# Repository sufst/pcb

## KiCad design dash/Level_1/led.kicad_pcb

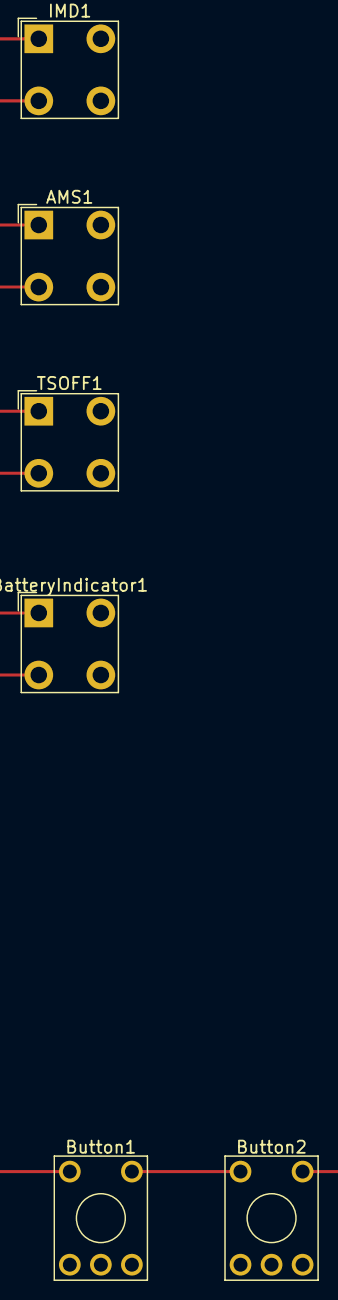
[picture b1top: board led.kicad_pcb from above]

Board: 2 copper layers, 6 parts (0 on the bottom side), 2 nets.

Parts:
AMS1: LED; LED_BL-FL7680RGB
BatteryIndicator1: LED; LED_BL-FL7680RGB
Button1: TS ON; KSA_Tactile_SPST
Button2: R2D; KSA_Tactile_SPST
IMD1: LED; LED_BL-FL7680RGB
TSOFF1: LED; LED_BL-FL7680RGB

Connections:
GND: AMS1.1, BatteryIndicator1.1, IMD1.1, TSOFF1.1
Precharge: Button1.2, Button2.1

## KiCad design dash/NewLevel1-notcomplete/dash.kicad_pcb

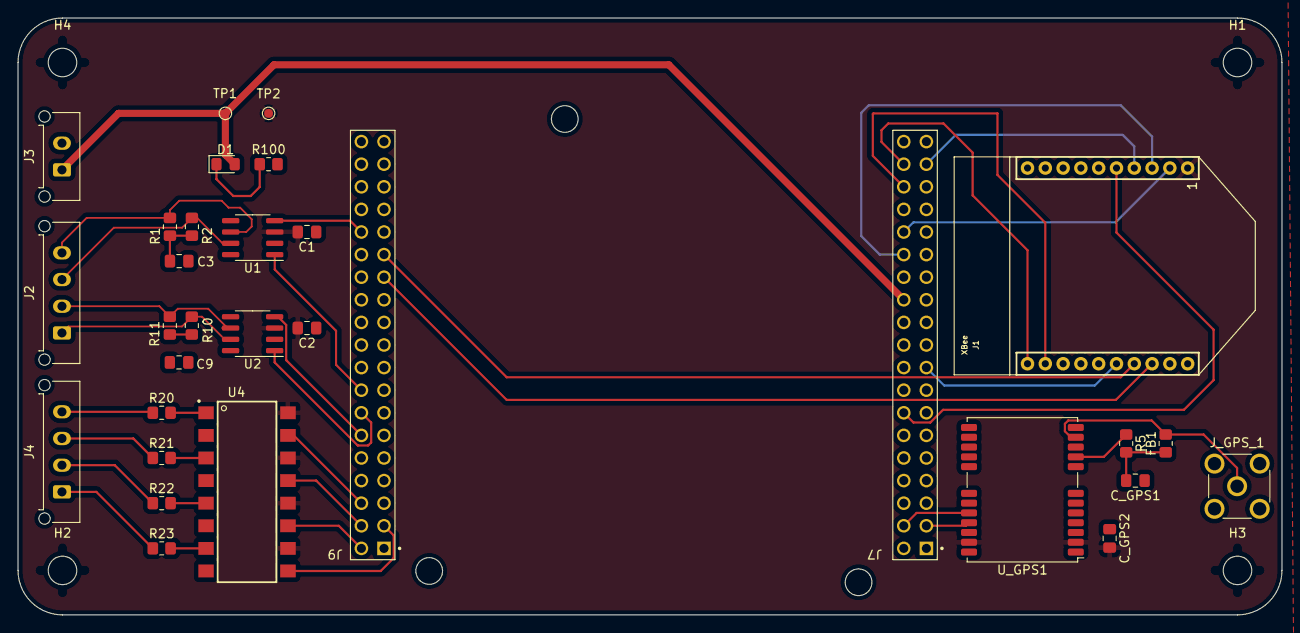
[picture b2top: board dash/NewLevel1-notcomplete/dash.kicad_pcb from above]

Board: 2 copper layers, 142.1 x 67.1 mm, 35 parts (0 on the bottom side), 40 nets.

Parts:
C1, C2: 100n; C_0805_2012Metric_Pad1.18x1.45mm_HandSolder
C3, C9: 4.7n; C_0805_2012Metric_Pad1.18x1.45mm_HandSolder
C_GPS1: 47pF; C_0805_2012Metric_Pad1.18x1.45mm_HandSolder
C_GPS2: 100nF; C_0805_2012Metric_Pad1.18x1.45mm_HandSolder
D1: LED; LED_0805_2012Metric_Pad1.15x1.40mm_HandSolder
FB1: 120; R_0805_2012Metric_Pad1.20x1.40mm_HandSolder
H1, H2, H3, H4: M3; MountingHole_3.2mm_M3
J1: XBee; XBEE
J2: CAN; Molex_Micro-Fit_3.0_43650-0415_1x04_P3.00mm_Vertical
J3: PWR; Molex_Micro-Fit_3.0_43650-0215_1x02_P3.00mm_Vertical
J4: MCU_DIN; Molex_Micro-Fit_3.0_43650-0415_1x04_P3.00mm_Vertical
J7: CN7; NUCLEO-F446RE-2x19-CON
J9: CN10; NUCLEO-F446RE-2x19-CON
J_GPS_1: Conn_Coaxial; SMA_Molex_73251-2200_Horizontal
R1, R2, R10, R11: 60R; R_0805_2012Metric_Pad1.20x1.40mm_HandSolder
R5: 33; R_0805_2012Metric_Pad1.20x1.40mm_HandSolder
R20, R21, R22, R23: 1k; R_0805_2012Metric_Pad1.20x1.40mm_HandSolder
R100: 3.3k; R_0805_2012Metric_Pad1.20x1.40mm_HandSolder
TP1: 12V; TestPoint_Pad_D1.0mm
TP2: 3V3; TestPoint_Pad_D1.0mm
U1, U2: MAX3051ESA+; SOIC-8_3.9x4.9mm_P1.27mm
U4: ILQ615-4X009T; SOIC254P1005X380-16N
U_GPS1: NEO-M9N; ublox_NEO

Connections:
+3V3: C1.2, C2.2, C_GPS2.2, J1.1, J7.16, TP2.1, U1.3 (VDD), U2.3 (VDD), U4.10, U4.12, U4.14, U4.16, U_GPS1.2 (D_SEL), U_GPS1.23 (VCC)
+12V: D1.2 (A), J3.1, J7.24, TP1.1
/CAN-C Bus Transceiver/CAN_RX: J9.12, U2.4 (RXD)
/CAN-C Bus Transceiver/CAN_TX: J9.14, U2.1 (TXD)
/CAN-S Bus Transceiver/CAN_RX: J9.30, U1.4 (RXD)
/CAN-S Bus Transceiver/CAN_TX: J9.16, U1.1 (TXD)
/CAN_C+: J2.1, R10.2, U2.7 (CANH)
/CAN_C-: J2.2, R11.1, U2.6 (CANL)
/CAN_S+: J2.3, R1.2, U1.7 (CANH)
/CAN_S-: J2.4, R2.1, U1.6 (CANL)
/EXTRA_IN_1: J4.4, R20.1
/EXTRA_IN_2: J4.3, R21.1
/EXTRA_IN_3: J4.2, R22.1
/EXTRA_IN_4: J4.1, R23.1
/GPS/GPS_RX: J7.3, U_GPS1.21 (RXD/SPI_MOSI)
/GPS/GPS_TX: J7.4, U_GPS1.20 (TXD/SPI_MISO)
/XBee Module/DIN/`CONFIG/DIO14: J1.3, J7.28
/XBee Module/DOUT/DIO13: J1.2, J7.30
/XBee Module/SPI_CLK: J1.18, J9.25
/XBee Module/SPI_MISO: J1.4, J7.35
/XBee Module/SPI_MOSI: J1.11, J7.36
/XBee Module/SPI_~SSEL: J1.17, J9.27
/XBee Module/~CTS: J1.12, J7.34
/XBee Module/~RESET: J1.5, J7.14
/XBee Module/~RTS: J1.16, J7.17
/input shift/EXTRA_OUT_1: J9.6, U4.15
/input shift/EXTRA_OUT_2: J9.4, U4.13
/input shift/EXTRA_OUT_3: J9.2, U4.11
/input shift/EXTRA_OUT_4: J9.3, U4.9
GND: C1.1, C2.1, C3.2, C9.2, C_GPS1.1, C_GPS2.1, J1.10, J3.2, J7.8, J7.19, J7.20, J7.22, J9.9, J9.20, J_GPS_1.2 (Ext), R100.2, U1.2 (GND), U1.8 (RS), U2.2 (GND), U2.8 (RS), U4.2, U4.4, U4.6, U4.8, U_GPS1.10 (GND), U_GPS1.12 (GND), U_GPS1.13 (GND), U_GPS1.24 (GND)
unnamed: C3.1, R1.1, R2.2
unnamed: C9.1, R10.1, R11.2
unnamed: C_GPS1.2, FB1.1, R5.2
unnamed: D1.1 (K), R100.1
unnamed: FB1.2, J_GPS_1.1 (In), U_GPS1.11 (RF_IN)
unnamed: R5.1, U_GPS1.9 (VCC_RF)
unnamed: R20.2, U4.1
unnamed: R21.2, U4.3
unnamed: R22.2, U4.5
unnamed: R23.2, U4.7

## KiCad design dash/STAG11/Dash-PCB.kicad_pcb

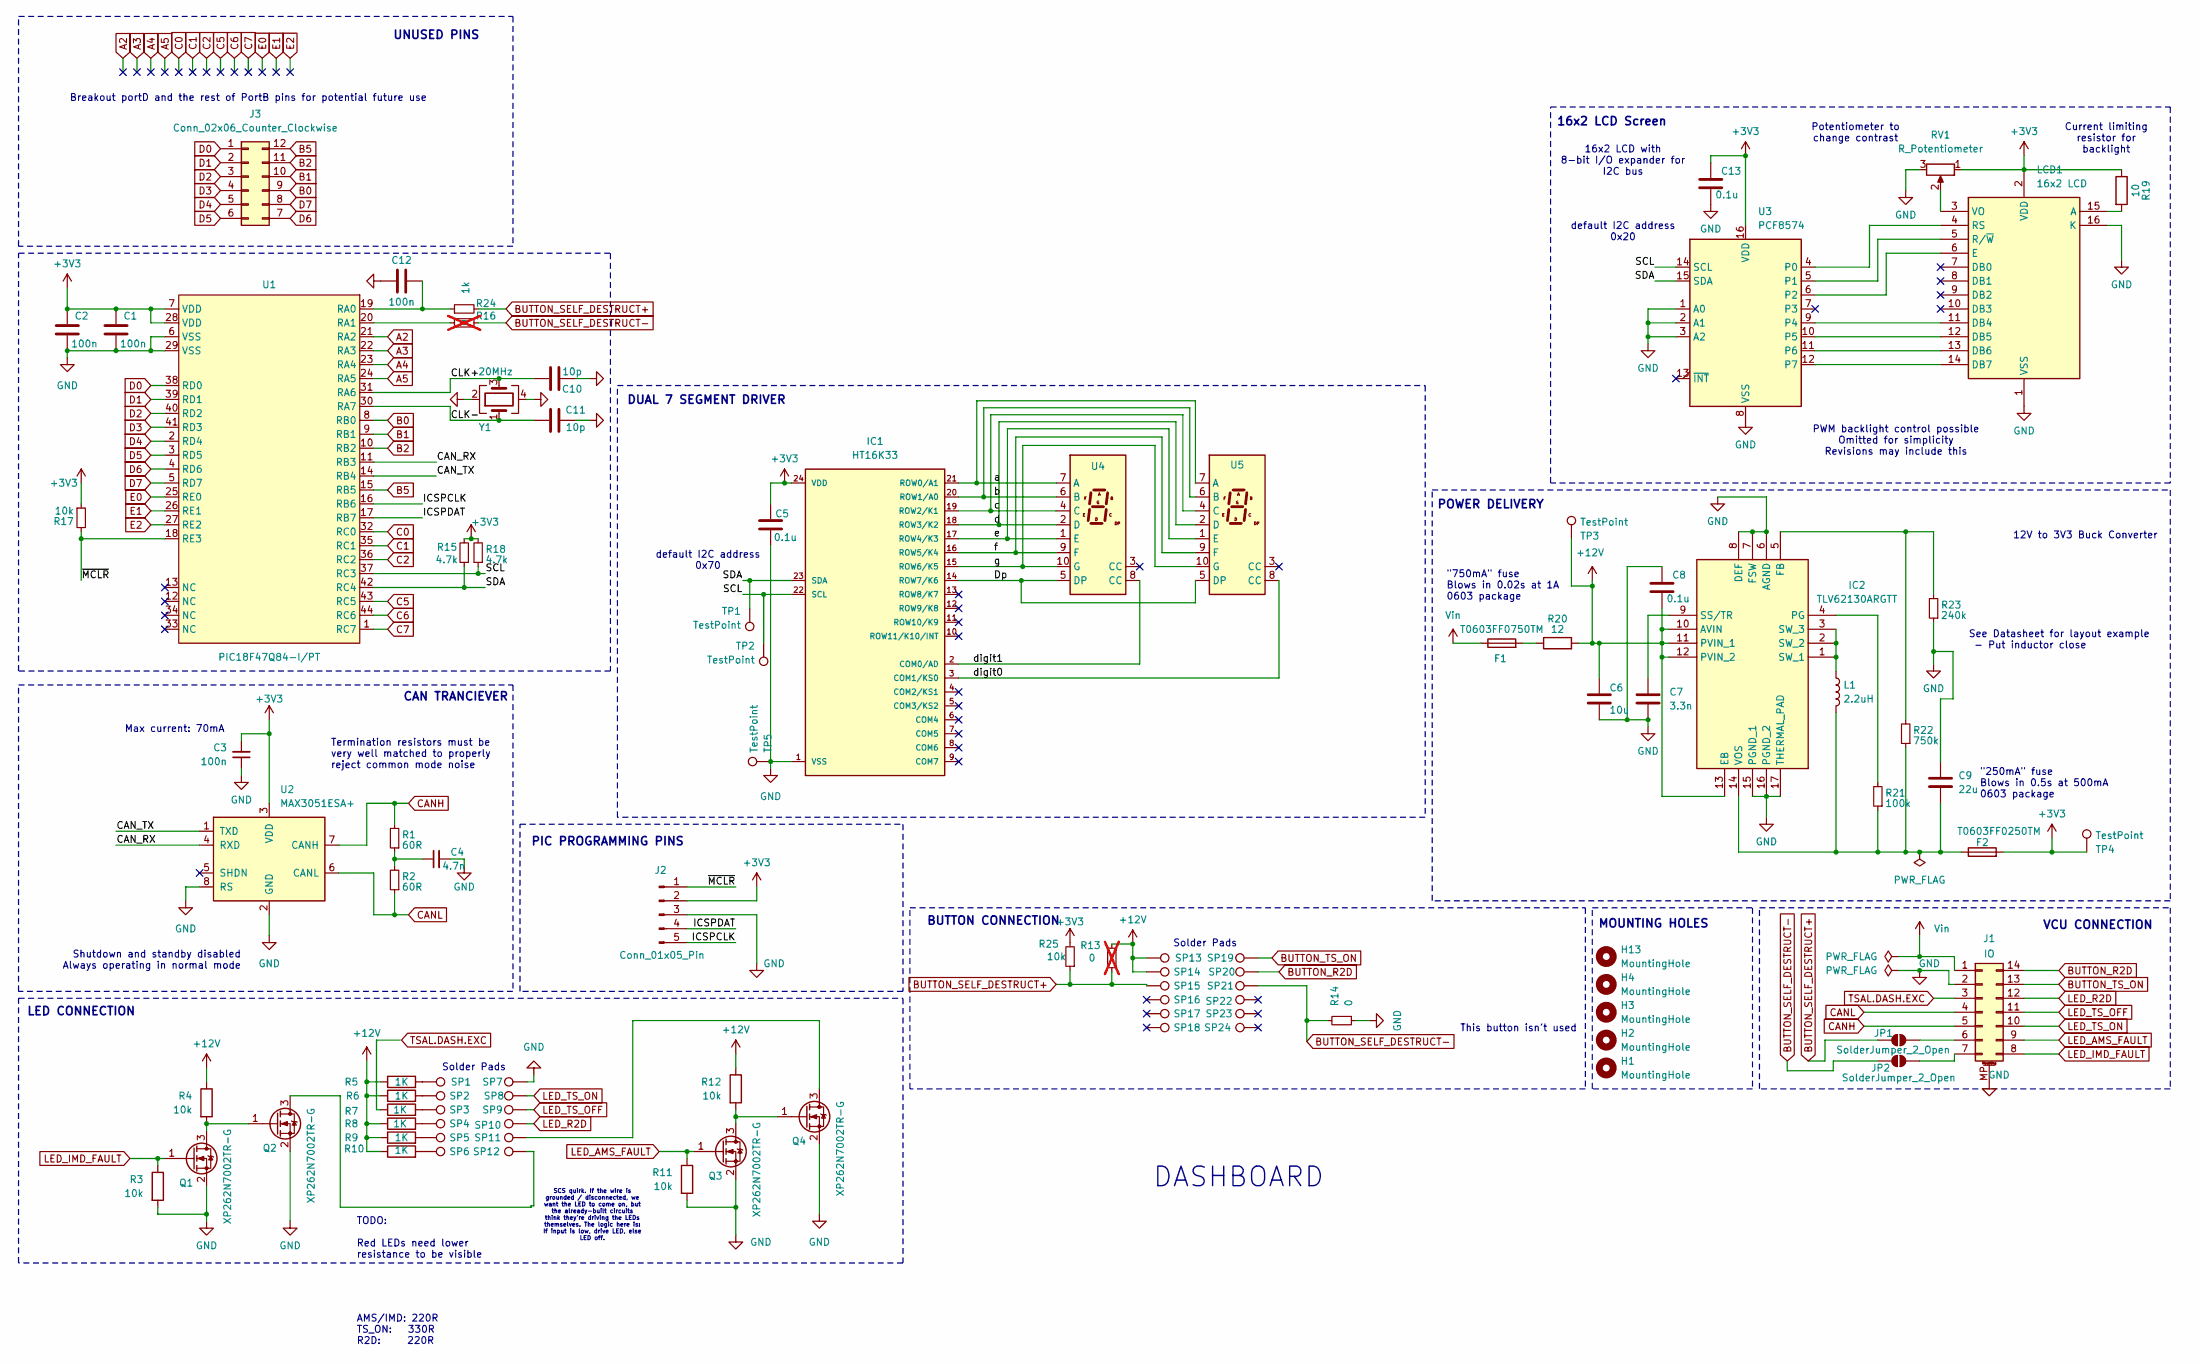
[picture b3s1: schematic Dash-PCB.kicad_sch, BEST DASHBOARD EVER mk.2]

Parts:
C1, C2, C3: 100n; C_0805_2012Metric_Pad1.18x1.45mm_HandSolder
C4: 4.7n; C_0805_2012Metric_Pad1.18x1.45mm_HandSolder
C5, C8, C13: 0.1u; C_0805_2012Metric_Pad1.18x1.45mm_HandSolder
C6: 10u; C_0805_2012Metric_Pad1.18x1.45mm_HandSolder
C7: 3.3n; C_0805_2012Metric_Pad1.18x1.45mm_HandSolder
C9: 22u; C_0805_2012Metric_Pad1.18x1.45mm_HandSolder
C10, C11: 10p; C_0603_1608Metric_Pad1.08x0.95mm_HandSolder; Manufacturer_Part_Number C0805C100J1RACAUTO; Mouser Part Number 80-C0805C100J1RAUTO
C12: 100n; C_0603_1608Metric_Pad1.08x0.95mm_HandSolder; Manufacturer_Part_Number C0805C100J1RACAUTO; Mouser Part Number 80-C0805C100J1RAUTO
F1: T0603FF0750TM; Fuse_0603_1608Metric_Pad1.05x0.95mm_HandSolder
F2: T0603FF0250TM; Fuse_0603_1608Metric_Pad1.05x0.95mm_HandSolder
H1, H2, H3, H4, H13: MountingHole; MountingHole_4.3mm_M4
IC1: HT16K33
IC2: TLV62130ARGTT; QFN50P300X300X100-17N-D; Mouser Part Number 595-TLV62130ARGTT
J1: IO; Molex_Micro-Fit_3.0_43045-1418_2x07-1MP_P3.00mm_Vertical
J2: Conn_01x05_Pin; PinSocket_1x05_P2.54mm_Vertical
J3: Conn_02x06_Counter_Clockwise; PinHeader_2x06_P2.54mm_Vertical
JP1, JP2: SolderJumper_2_Open; SolderJumper-2_P1.3mm_Open_RoundedPad1.0x1.5mm
L1: 2.2uH; IHLP1212BZEV2R2M11
LCD1: 16x2 LCD; Mouser Part Number 426-FIT0127
Q1, Q2, Q3, Q4: XP262N7002TR-G; SOT-23
R1, R2: 60R; R_0805_2012Metric_Pad1.20x1.40mm_HandSolder
R3, R4, R11, R12, R17, R25: 10k; R_0805_2012Metric_Pad1.20x1.40mm_HandSolder
R5, R6, R7, R8, R9, R10: 1K; R_0805_2012Metric_Pad1.20x1.40mm_HandSolder
R13, R16: 0; R_0805_2012Metric_Pad1.20x1.40mm_HandSolder; not fitted
R14: 0; R_0805_2012Metric_Pad1.20x1.40mm_HandSolder
R15, R18: 4.7k; R_0805_2012Metric_Pad1.20x1.40mm_HandSolder
R19: 10; R_0805_2012Metric_Pad1.20x1.40mm_HandSolder
R20: 12; R_0805_2012Metric_Pad1.20x1.40mm_HandSolder
R21: 100k; R_0805_2012Metric_Pad1.20x1.40mm_HandSolder
R22: 750k; R_0805_2012Metric_Pad1.20x1.40mm_HandSolder
R23: 240k; R_0805_2012Metric_Pad1.20x1.40mm_HandSolder
R24: 1k; R_0805_2012Metric_Pad1.20x1.40mm_HandSolder
RV1: R_Potentiometer; TS7Y103KR32
SP1, SP2, SP3, SP4, SP5, SP6, SP7, SP8, SP9, SP10, SP11, SP12, SP13, SP14, SP15, SP16, SP17, SP18, SP19, SP20, SP21, SP22, SP23, SP24: Solder Pad; TestPoint_Pad_D2.0mm
TP1, TP2, TP3, TP4, TP5: TestPoint; TestPoint_THTPad_D2.5mm_Drill1.2mm
U1: PIC18F47Q84-I/PT; TQFP-44_10x10mm_P0.8mm
U2: MAX3051ESA+; SOIC-8_3.9x4.9mm_P1.27mm
U3: PCF8574; SOIC127P1030X265-16N
U4, U5: Generic 7 seg 20mmx27.7mm
Y1: 20MHz; Crystal_SMD_SeikoEpson_FA128-4Pin_2.0x1.6mm; Manufacturer_Part_Number FA-128 20.00M-A0AAYYG80RE0; Mouser Part Number 732-FA12820A0AAYYG80

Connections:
+3V3: C1.1, C2.1, C3.2, C5.1, C13.1, F2.2, IC1.24 (VDD), J2.2, LCD1.2 (VDD), R15.2, R17.1, R18.2, R19.1, R25.2, RV1.1, TP4.1, U1.7 (VDD), U1.28 (VDD), U2.3 (VDD), U3.16 (VDD)
+12V: C6.1, C8.2, IC2.10 (AVIN), IC2.11 (PVIN_1), IC2.12 (PVIN_2), IC2.13 (EB), R4.1, R5.1, R6.1, R7.1, R8.1, R9.1, R10.1, R12.1, R13.2, R20.2, SP13.1, SP14.1, TP3.1
/CAN_RX: U1.11 (RB3), U2.4 (RXD)
/CAN_TX: U1.14 (RB4), U2.1 (TXD)
/CLK+: C10.1, U1.31 (RA6), Y1.3
/CLK-: C11.1, U1.30 (RA7), Y1.1
/Dp: IC1.14 (ROW7/K6), U4.5 (DP), U5.5 (DP)
/ICSPCLK: J2.5, U1.16 (RB6)
/ICSPDAT: J2.4, U1.17 (RB7)
/SCL: IC1.22 (SCL), R18.1, TP2.1, U1.37 (RC3), U3.14 (SCL)
/SDA: IC1.23 (SDA), R15.1, TP1.1, U1.42 (RC4), U3.15 (SDA)
/a: IC1.21 (ROW0/A1), U4.7 (A), U5.7 (A)
/b: IC1.20 (ROW1/A0), U4.6 (B), U5.6 (B)
/c: IC1.19 (ROW2/K1), U4.4 (C), U5.4 (C)
/d: IC1.18 (ROW3/K2), U4.2 (D), U5.2 (D)
/digit0: IC1.3 (COM1/KS0), U5.8 (CC)
/digit1: IC1.2 (COM0/AD), U4.8 (CC)
/e: IC1.17 (ROW4/K3), U4.1 (E), U5.1 (E)
/f: IC1.16 (ROW5/K4), U4.9 (F), U5.9 (F)
/g: IC1.15 (ROW6/K5), U4.10 (G), U5.10 (G)
/~MCLR: J2.1, R17.2, U1.18 (RE3)
A2: U1.21 (RA2)
A3: U1.22 (RA3)
A4: U1.23 (RA4)
A5: U1.24 (RA5)
B0: J3.9, U1.8 (RB0)
B1: J3.10, U1.9 (RB1)
B2: J3.11, U1.10 (RB2)
B5: J3.12, U1.15 (RB5)
BUTTON_R2D: J1.14, SP20.1
BUTTON_SELF_DESTRUCT+: JP1.1 (A), R13.1, R24.2, R25.1, SP15.1
BUTTON_SELF_DESTRUCT-: JP2.1 (A), R14.2, R16.2, SP21.1
BUTTON_TS_ON: J1.13, SP19.1
C0: U1.32 (RC0)
C1: U1.35 (RC1)
C2: U1.36 (RC2)
C5: U1.43 (RC5)
C6: U1.44 (RC6)
C7: U1.1 (RC7)
CANH: J1.5, R1.2, U2.7 (CANH)
CANL: J1.4, R2.1, U2.6 (CANL)
D0: J3.1, U1.38 (RD0)
D1: J3.2, U1.39 (RD1)
D2: J3.3, U1.40 (RD2)
D3: J3.4, U1.41 (RD3)
D4: J3.5, U1.2 (RD4)
D5: J3.6, U1.3 (RD5)
D6: J3.7, U1.4 (RD6)
D7: J3.8, U1.5 (RD7)
E0: U1.25 (RE0)
E1: U1.26 (RE1)
E2: U1.27 (RE2)
GND: C1.2, C2.2, C3.1, C4.2, C5.2, C6.2, C7.2, C8.1, C9.1, C10.2, C11.2, C12.2, C13.2, IC1.1 (VSS), IC2.6 (AGND), IC2.7 (FSW), IC2.8 (DEF), IC2.15 (PGND_1), IC2.16 (PGND_2), IC2.17 (THERMAL_PAD), J1.2, J1.MP (MountPin), J2.3, LCD1.1 (VSS), LCD1.16 (K), Q1.2 (S), Q2.2 (S), Q3.2 (S), Q4.2 (S), R3.2, R11.2, R14.1, R23.1, RV1.3, SP7.1, TP5.1, U1.6 (VSS), U1.29 (VSS), U2.2 (GND), U2.8 (RS), U3.1 (A0), U3.2 (A1), U3.3 (A2), U3.8 (VSS), Y1.2, Y1.4
LED_AMS_FAULT: J1.9, Q3.1 (G), R11.1
LED_IMD_FAULT: J1.8, Q1.1 (G), R3.1
LED_R2D: J1.12, SP10.1
LED_TS_OFF: J1.11, SP9.1
LED_TS_ON: J1.10, SP8.1
unnamed: C4.1, R1.1, R2.2
unnamed: F1.2, R20.1
unnamed: IC2.5 (FB), R22.2, R23.2
unnamed: IC2.4 (PG), R21.2
unnamed: C7.1, IC2.9 (SS/TR)
unnamed: IC2.1 (SW_1), IC2.2 (SW_2), IC2.3 (SW_3), L1.1
unnamed: C9.2, F2.1, IC2.14 (VOS), L1.2, R21.1, R22.1
unnamed: J1.6, JP1.2 (B)
unnamed: J1.7, JP2.2 (B)
unnamed: LCD1.15 (A), R19.2
unnamed: LCD1.11 (DB4), U3.9 (P4)
unnamed: LCD1.12 (DB5), U3.10 (P5)
unnamed: LCD1.13 (DB6), U3.11 (P6)
unnamed: LCD1.14 (DB7), U3.12 (P7)
unnamed: LCD1.6 (E), U3.6 (P2)
unnamed: LCD1.4 (RS), U3.4 (P0)
unnamed: LCD1.5 (R/~W), U3.5 (P1)
unnamed: LCD1.3 (VO), RV1.2
unnamed: Q1.3 (D), Q2.1 (G), R4.2
unnamed: Q2.3 (D), SP12.1
unnamed: Q3.3 (D), Q4.1 (G), R12.2
unnamed: Q4.3 (D), SP11.1
unnamed: R5.2, SP1.1
unnamed: R6.2, SP2.1
unnamed: R7.2, SP3.1
unnamed: R8.2, SP4.1
unnamed: R9.2, SP5.1
unnamed: R10.2, SP6.1
unnamed: C12.1, R24.1, U1.19 (RA0)
unnamed: R16.1, U1.20 (RA1)
Vin: F1.1, J1.1

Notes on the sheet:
Solder Pads
default I2C address 0x20
LED CONNECTION
TODO: Red LEDs need lower resistance to be visible
SCS quirk. If the wire is grounded / disconnected, we want the LED to come on, but the already-built circuits think they're driving the LEDs themselves. The logic here is: If input is low, drive LED, else LED off.
MOUNTING HOLES
CAN TRANCIEVER
Current limiting resistor for backlight
"750mA" fuse Blows in 0.02s at 1A 0603 package
AMS/IMD: 220R TS_ON: 330R R2D: 220R
VCU CONNECTION
PWM backlight control possible Omitted for simplicity Revisions may include this
"250mA" fuse Blows in 0.5s at 500mA 0603 package
default I2C address 0x70
DUAL 7 SEGMENT DRIVER
POWER DELIVERY
Breakout portD and the rest of PortB pins for potential future use
12V to 3V3 Buck Converter
16x2 LCD with 8-bit I/O expander for I2C bus
BUTTON CONNECTION
This button isn't used
PIC PROGRAMMING PINS
UNUSED PINS
Shutdown and standby disabled Always operating in normal mode
Potentiometer to change contrast
See Datasheet for layout example - Put inductor close
16x2 LCD Screen
Termination resistors must be very well matched to properly reject common mode noise
DASHBOARD
Max current: 70mA

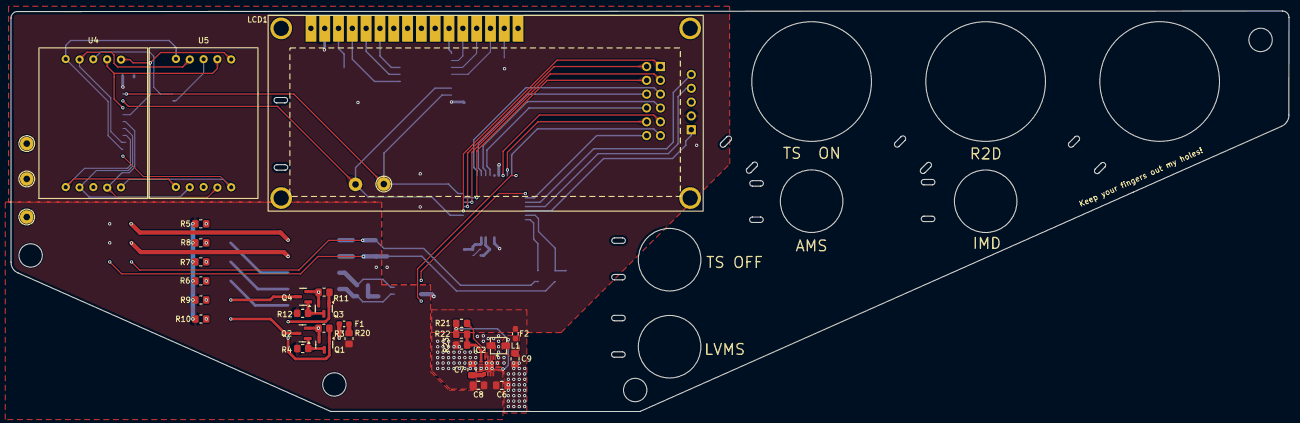
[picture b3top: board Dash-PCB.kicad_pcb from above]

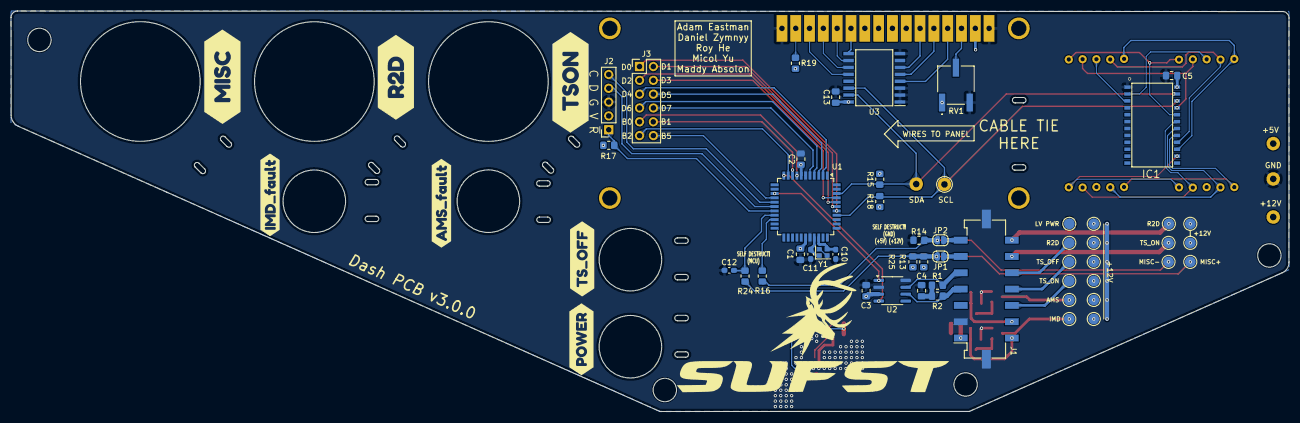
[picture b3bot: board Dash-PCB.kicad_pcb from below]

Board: 2 copper layers, 235.0 x 73.6 mm, 94 parts (57 on the bottom side), 76 nets.

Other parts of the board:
kibuzzard-67F6B156: G***; kibuzzard-67F6B156
kibuzzard-67F52EB7: G***; kibuzzard-67F52EB7
kibuzzard-67F52EF3: G***; kibuzzard-67F52EF3
kibuzzard-67F52FB1: G***; kibuzzard-67F52FB1
kibuzzard-67F52FD7: G***; kibuzzard-67F52FD7
kibuzzard-67F5305C: G***; kibuzzard-67F5305C
kibuzzard-67F53054: G***; kibuzzard-67F53054

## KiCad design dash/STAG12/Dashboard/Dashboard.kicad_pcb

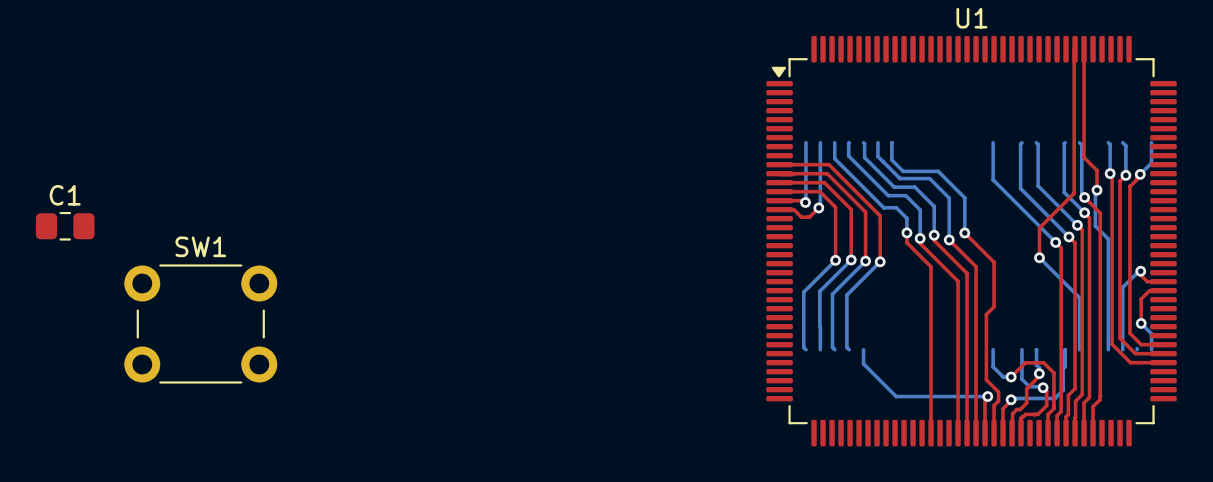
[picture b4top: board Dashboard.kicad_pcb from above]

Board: 2 copper layers, 4 parts (1 on the bottom side), 35 nets.

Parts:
C1: 100n; C_0805_2012Metric_Pad1.18x1.45mm_HandSolder
SW1: SW_Push; SW_PUSH_6mm
U1: STM32F746ZGTx; LQFP-144_20x20mm_P0.5mm
U2: W9812G6KH-5; TSOP-II-54_22.2x10.16mm_P0.8mm

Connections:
+3V3: U1.6 (VBAT), U1.17 (VDD), U1.30 (VDD), U1.33 (VDDA), U1.39 (VDD), U1.52 (VDD), U1.62 (VDD), U1.72 (VDD), U1.84 (VDD), U1.95 (VDDUSB), U1.108 (VDD), U1.121 (VDD), U1.131 (VDD), U1.144 (VDD)
/STM32F746ZG/NRST: C1.1, SW1.2, U1.25 (NRST)
/STM32F746ZG/RAM_A0: U1.10 (PF0), U2.23 (A0)
/STM32F746ZG/RAM_A1: U1.11 (PF1), U2.24 (A1)
/STM32F746ZG/RAM_A2: U1.12 (PF2), U2.25 (A2)
/STM32F746ZG/RAM_A3: U1.13 (PF3), U2.26 (A3)
/STM32F746ZG/RAM_A4: U1.14 (PF4), U2.29 (A4)
/STM32F746ZG/RAM_A5: U1.15 (PF5), U2.30 (A5)
/STM32F746ZG/RAM_A6: U1.50 (PF12), U2.31 (A6)
/STM32F746ZG/RAM_A7: U1.53 (PF13), U2.32 (A7)
/STM32F746ZG/RAM_A8: U1.54 (PF14), U2.33 (A8)
/STM32F746ZG/RAM_A9: U1.55 (PF15), U2.34 (A9)
/STM32F746ZG/RAM_A10: U1.56 (PG0), U2.22 (A10/AP)
/STM32F746ZG/RAM_A11: U1.57 (PG1), U2.35 (A11)
/STM32F746ZG/RAM_D0: U1.85 (PD14), U2.2 (DQ0)
/STM32F746ZG/RAM_D1: U1.86 (PD15), U2.4 (DQ1)
/STM32F746ZG/RAM_D2: U1.114 (PD0), U2.5 (DQ2)
/STM32F746ZG/RAM_D3: U1.115 (PD1), U2.7 (DQ3)
/STM32F746ZG/RAM_D4: U1.58 (PE7), U2.8 (DQ4)
/STM32F746ZG/RAM_D5: U1.59 (PE8), U2.10 (DQ5)
/STM32F746ZG/RAM_D6: U1.60 (PE9), U2.11 (DQ6)
/STM32F746ZG/RAM_D7: U1.63 (PE10), U2.13 (DQ7)
/STM32F746ZG/RAM_D8: U1.64 (PE11), U2.42 (DQ8)
/STM32F746ZG/RAM_D9: U1.65 (PE12), U2.44 (DQ9)
/STM32F746ZG/RAM_D10: U1.66 (PE13), U2.45 (DQ10)
/STM32F746ZG/RAM_D11: U1.67 (PE14), U2.47 (DQ11)
/STM32F746ZG/RAM_D12: U1.68 (PE15), U2.48 (DQ12)
/STM32F746ZG/RAM_D13: U1.77 (PD8), U2.50 (DQ13)
/STM32F746ZG/RAM_D14: U1.78 (PD9), U2.51 (DQ14)
/STM32F746ZG/RAM_D15: U1.79 (PD10), U2.53 (DQ15)
GND: C1.2, SW1.1, U1.16 (VSS), U1.31 (VSSA), U1.38 (VSS), U1.51 (VSS), U1.61 (VSS), U1.83 (VSS), U1.94 (VSS), U1.107 (VSS), U1.120 (VSS), U1.130 (VSS)
unnamed: U2.1 (VDD), U2.14 (VDD), U2.27 (VDD)
unnamed: U2.3 (VDDQ), U2.9 (VDDQ), U2.43 (VDDQ), U2.49 (VDDQ)
unnamed: U2.28 (VSS), U2.41 (VSS), U2.54 (VSS)
unnamed: U2.6 (VSSQ), U2.12 (VSSQ), U2.46 (VSSQ), U2.52 (VSSQ)

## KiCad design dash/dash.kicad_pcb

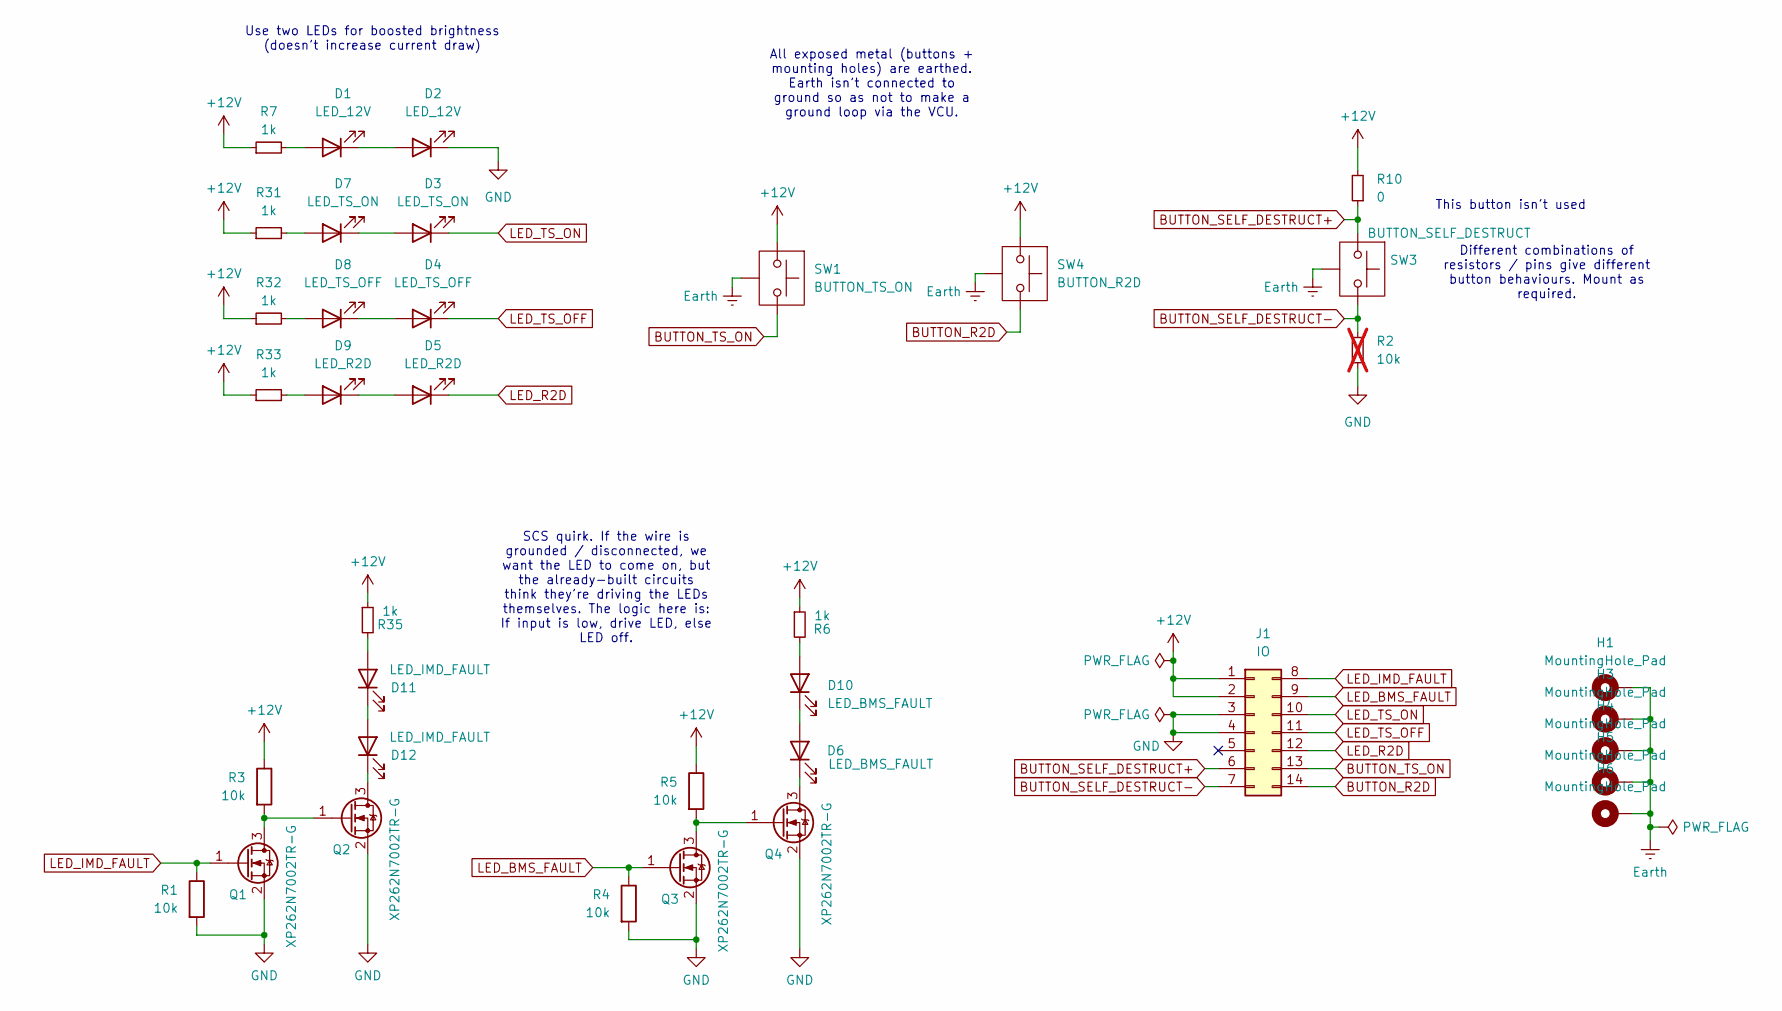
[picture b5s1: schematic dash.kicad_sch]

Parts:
D1, D2: LED_12V; LED_0805_2012Metric_Pad1.15x1.40mm_HandSolder
D3, D7: LED_TS_ON; LED_0805_2012Metric_Pad1.15x1.40mm_HandSolder
D4, D8: LED_TS_OFF; LED_0805_2012Metric_Pad1.15x1.40mm_HandSolder
D5, D9: LED_R2D; LED_0805_2012Metric_Pad1.15x1.40mm_HandSolder
D6, D10: LED_BMS_FAULT; LED_0805_2012Metric_Pad1.15x1.40mm_HandSolder
D11, D12: LED_IMD_FAULT; LED_0805_2012Metric_Pad1.15x1.40mm_HandSolder
H1, H3, H4, H5, H6: MountingHole_Pad; MountingHole_4.3mm_M4_ISO7380_Pad_TopBottom
J1: IO; Molex_Micro-Fit_3.0_43045-1418_2x07-1MP_P3.00mm_Vertical
Q1, Q2, Q3, Q4: XP262N7002TR-G; SOT-23
R1, R3, R4, R5: 10k; R_0805_2012Metric_Pad1.20x1.40mm_HandSolder
R2: 10k; R_0805_2012Metric_Pad1.20x1.40mm_HandSolder; not fitted
R6, R7, R31, R32, R33, R35: 1k; R_2512_6332Metric_Pad1.40x3.35mm_HandSolder
R10: 0; R_0805_2012Metric_Pad1.20x1.40mm_HandSolder
SW1: BUTTON_TS_ON; Button_MPB16_CA
SW3: BUTTON_SELF_DESTRUCT; Button_MPB16_CA
SW4: BUTTON_R2D; Button_MPB16_CA

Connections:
+12V: J1.1, J1.2, R3.1, R5.1, R6.1, R7.1, R10.2, R31.1, R32.1, R33.1, R35.1, SW1.1, SW4.1
BUTTON_R2D: J1.14, SW4.2
BUTTON_SELF_DESTRUCT+: J1.6, R10.1, SW3.1
BUTTON_SELF_DESTRUCT-: J1.7, R2.2, SW3.2
BUTTON_TS_ON: J1.13, SW1.2
Earth: H1.1, H3.1, H4.1, H5.1, H6.1, SW1.3 (Casing), SW3.3 (Casing), SW4.3 (Casing)
GND: D2.1 (K), J1.3, J1.4, Q1.2 (S), Q2.2 (S), Q3.2 (S), Q4.2 (S), R1.2, R2.1, R4.2
LED_BMS_FAULT: J1.9, Q3.1 (G), R4.1
LED_IMD_FAULT: J1.8, Q1.1 (G), R1.1
LED_R2D: D5.1 (K), J1.12
LED_TS_OFF: D4.1 (K), J1.11
LED_TS_ON: D3.1 (K), J1.10
unnamed: D1.2 (A), R7.2
unnamed: D1.1 (K), D2.2 (A)
unnamed: D3.2 (A), D7.1 (K)
unnamed: D4.2 (A), D8.1 (K)
unnamed: D5.2 (A), D9.1 (K)
unnamed: D6.1 (K), Q4.3 (D)
unnamed: D7.2 (A), R31.2
unnamed: D8.2 (A), R32.2
unnamed: D9.2 (A), R33.2
unnamed: D10.2 (A), R6.2
unnamed: D6.2 (A), D10.1 (K)
unnamed: D11.2 (A), R35.2
unnamed: D11.1 (K), D12.2 (A)
unnamed: D12.1 (K), Q2.3 (D)
unnamed: Q1.3 (D), Q2.1 (G), R3.2
unnamed: Q3.3 (D), Q4.1 (G), R5.2

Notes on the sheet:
Different combinations of resistors / pins give different button behaviours. Mount as required.
All exposed metal (buttons + mounting holes) are earthed. Earth isn't connected to ground so as not to make a ground loop via the VCU.
This button isn't used
Use two LEDs for boosted brightness (doesn't increase current draw)
SCS quirk. If the wire is grounded / disconnected, we want the LED to come on, but the already-built circuits think they're driving the LEDs themselves. The logic here is: If input is low, drive LED, else LED off.

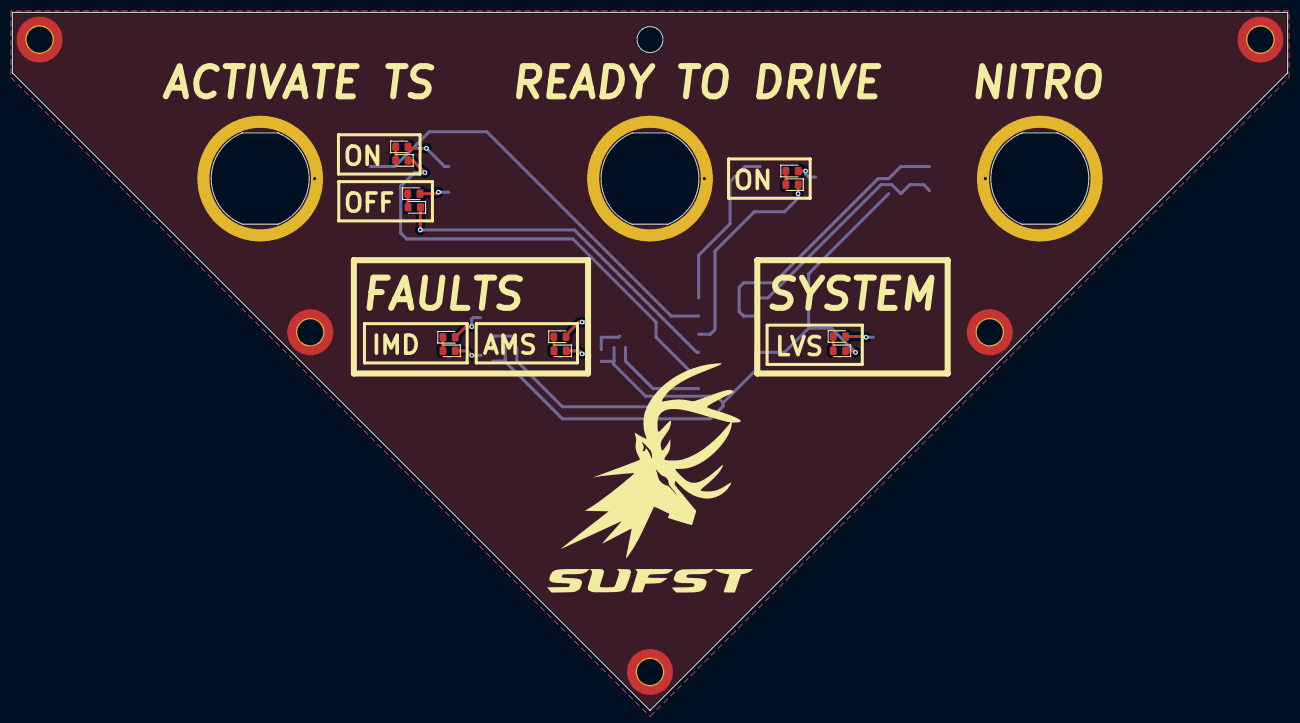
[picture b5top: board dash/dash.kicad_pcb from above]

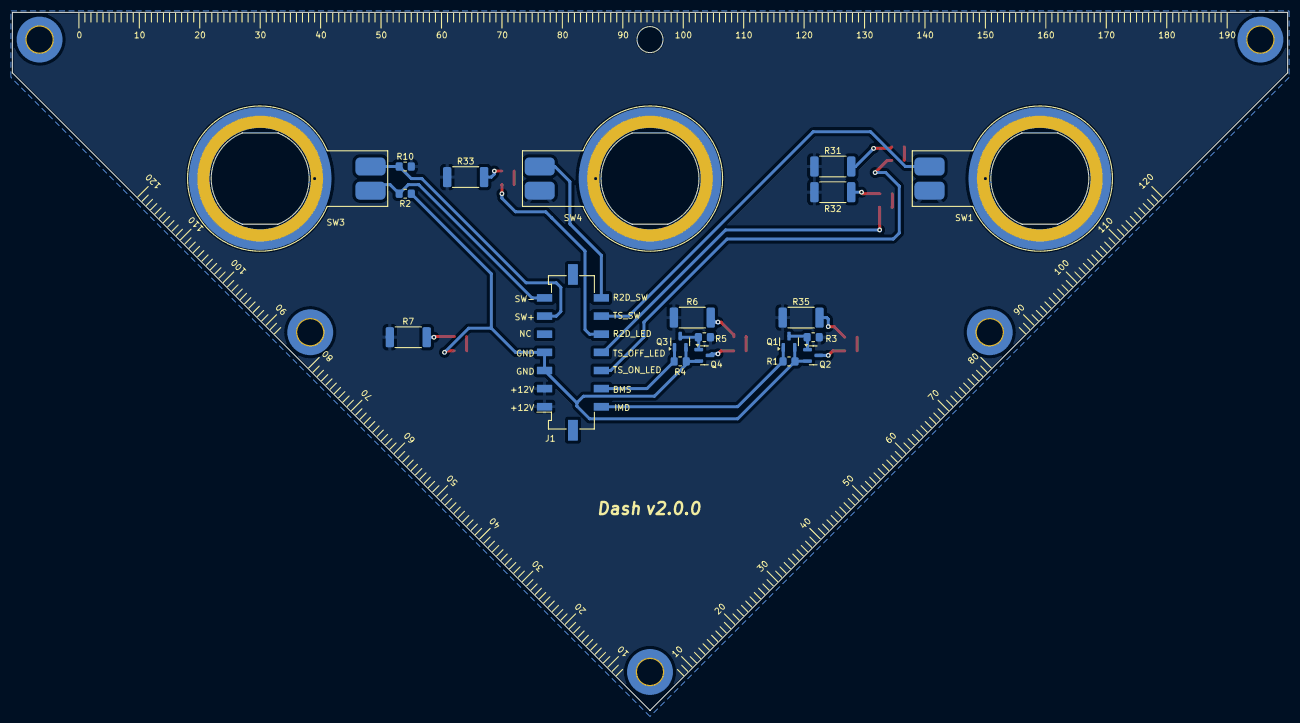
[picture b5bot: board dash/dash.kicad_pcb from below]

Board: 2 copper layers, 211.0 x 115.5 mm, 37 parts (17 on the bottom side), 28 nets.

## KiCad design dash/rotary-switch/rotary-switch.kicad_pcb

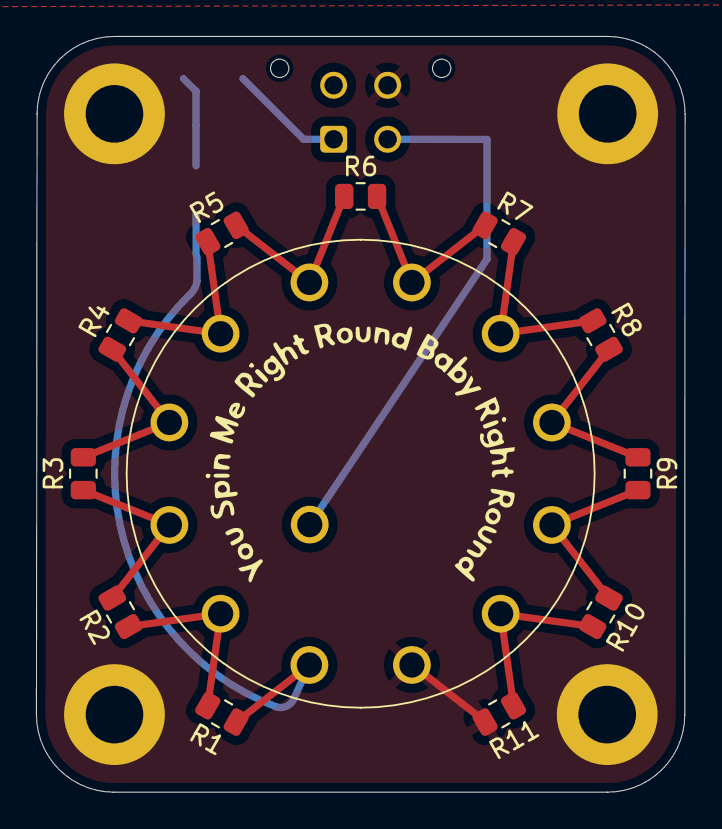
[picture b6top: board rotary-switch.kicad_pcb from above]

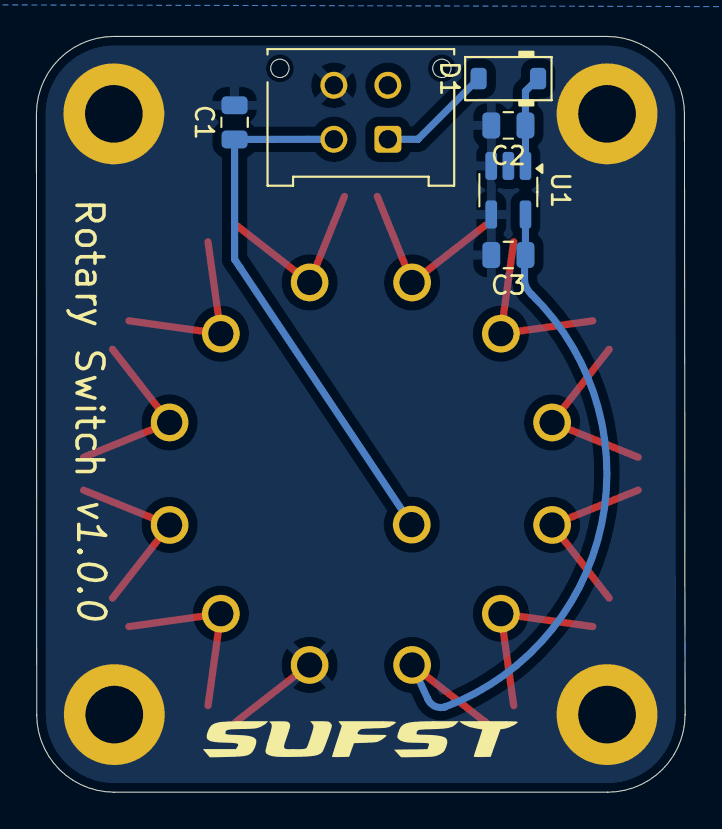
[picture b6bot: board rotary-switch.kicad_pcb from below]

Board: 2 copper layers, 36.0 x 42.0 mm, 22 parts (6 on the bottom side), 15 nets.

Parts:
C1: 1u; C_0805_2012Metric
C2: 10uF; C_0805_2012Metric
C3: 4.7uF; C_0805_2012Metric
D1: 1N5711W; D_SOD-123
H1, H2, H3, H4: MountingHole_Pad; MountingHole_3.2mm_M3_DIN965_Pad
J1: Conn_01x04_Socket; Molex_Micro-Fit_3.0_43045-0412_2x02_P3.00mm_Vertical
R1, R2, R3, R4, R5, R6, R7, R8, R9, R10, R11: 330; R_0805_2012Metric
SW1: SW_Rotary_1x12; ALPHA_12pos_rotary
U1: TPS7B6925-Q1; SOT-23-5_HandSoldering

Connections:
+3V3: C3.1, R1.1, SW1.1, U1.5 (OUT)
+GLV: D1.2 (A), J1.1
/Output: C1.1, J1.2, SW1.13
GND: C1.2, C2.2, C3.2, H1.1, H2.1, H3.1, H4.1, J1.4, R11.2, SW1.12, U1.3 (GND), U1.4 (GND)
unnamed: C2.1, D1.1 (K), U1.1 (IN)
unnamed: R1.2, R2.1, SW1.2
unnamed: R2.2, R3.1, SW1.3
unnamed: R3.2, R4.1, SW1.4
unnamed: R4.2, R5.1, SW1.5
unnamed: R5.2, R6.1, SW1.6
unnamed: R6.2, R7.1, SW1.7
unnamed: R7.2, R8.1, SW1.8
unnamed: R8.2, R9.1, SW1.9
unnamed: R9.2, R10.1, SW1.10
unnamed: R10.2, R11.1, SW1.11
